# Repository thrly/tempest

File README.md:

# TEMPEST

a 36/38-key split ergonomic keyboard

## Design

- Five columns, three rows, three thumb keys
  - Optional extra key for 36 or 38-key configuration (snap-off pcb)
- Column stagger and splay on the pinky and ring columns
- Powered by nice!nano / pro micro microcontroller
- Optional nice!view display
- Designed for wireless use + battery
- Low profile v1 Choc switches + hotswap sockets
- Reversible PCB
- Uses some components (JST plug, power switch, reset) from the Typeractive Corne design
- Layout designed with [Ergogen](https://ergogen.ceoloide.com/) (see [config.yaml](./ergogen/config.yaml))
- PCB designed with [KiCad](https://www.kicad.org/) (v 9)
- Simple 3D-printable case for both 36 and 38-key layouts

## Firmware

TEMPEST was designed to be used with ZMK. [You can find the ZMK-config repository and a keymap here.](https://github.com/thrly/tempest-zmk)

## Build Guide

[Details on the build and case can be found here.](/build-guide.md)

## Influences

TEMPEST is inspired by and takes influence from:

- [Temper](https://github.com/raeedcho/temper) by raeedcho
- [Bad Temper](https://github.com/essFitt/Bad-Temper/tree/main) by essFitt
- [TOTEM](https://github.com/GEIGEIGEIST/TOTEM) by GEIST
- [FORAGER](https://github.com/carrefinho/forager) by carrefinho
- [Corne](https://github.com/foostan/crkbd) by foostan (and the [Typeractive](https://typeractive.xyz/) version)
- also [Chocofi](https://github.com/pashutk/chocofi), [Sweep](https://github.com/davidphilipbarr/Sweep), and others.

## Thanks

If you build Tempest, I'd _love_ to hear how you get on with it. Please say hello via [thrly.com](https://www.thrly.com) or [instagram](https://www.instagram.com/thrly.xy/).

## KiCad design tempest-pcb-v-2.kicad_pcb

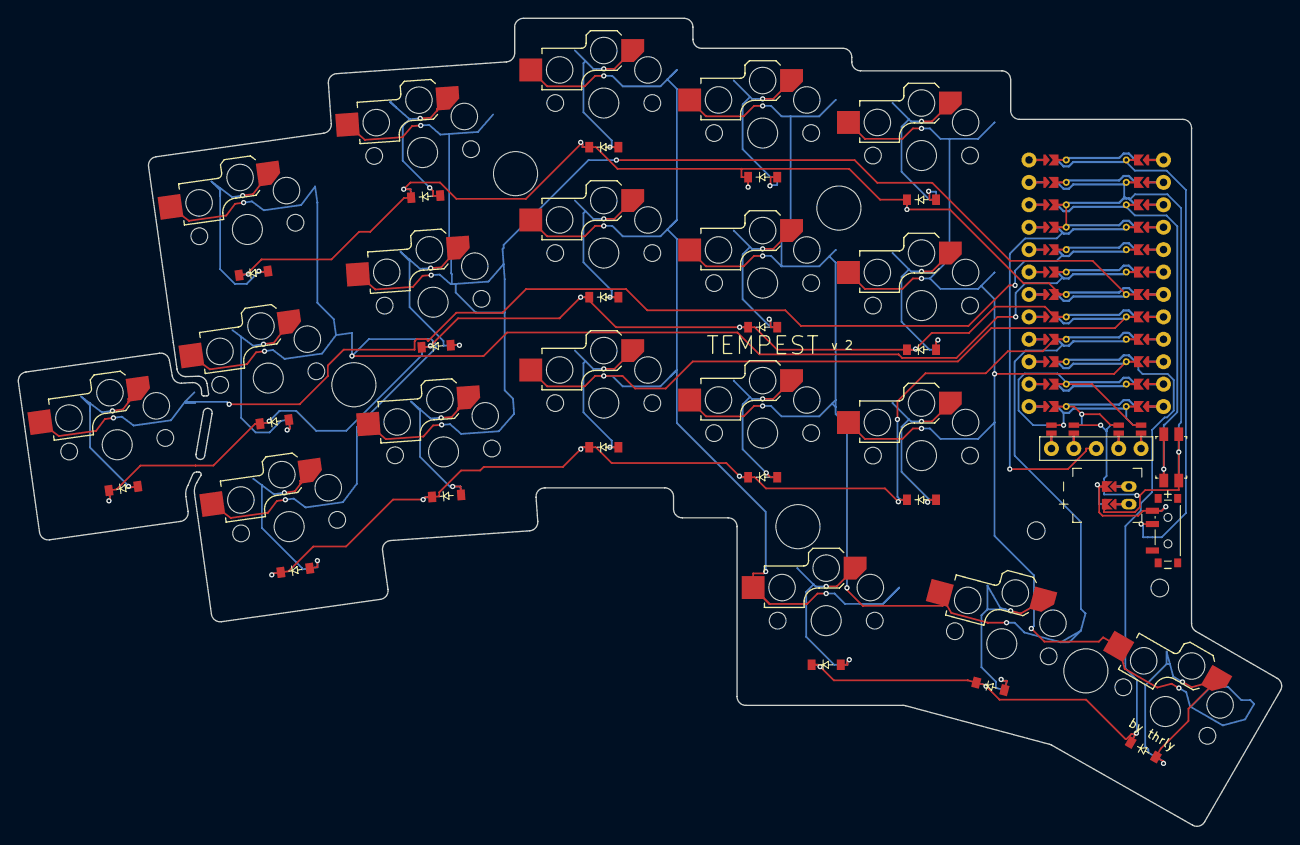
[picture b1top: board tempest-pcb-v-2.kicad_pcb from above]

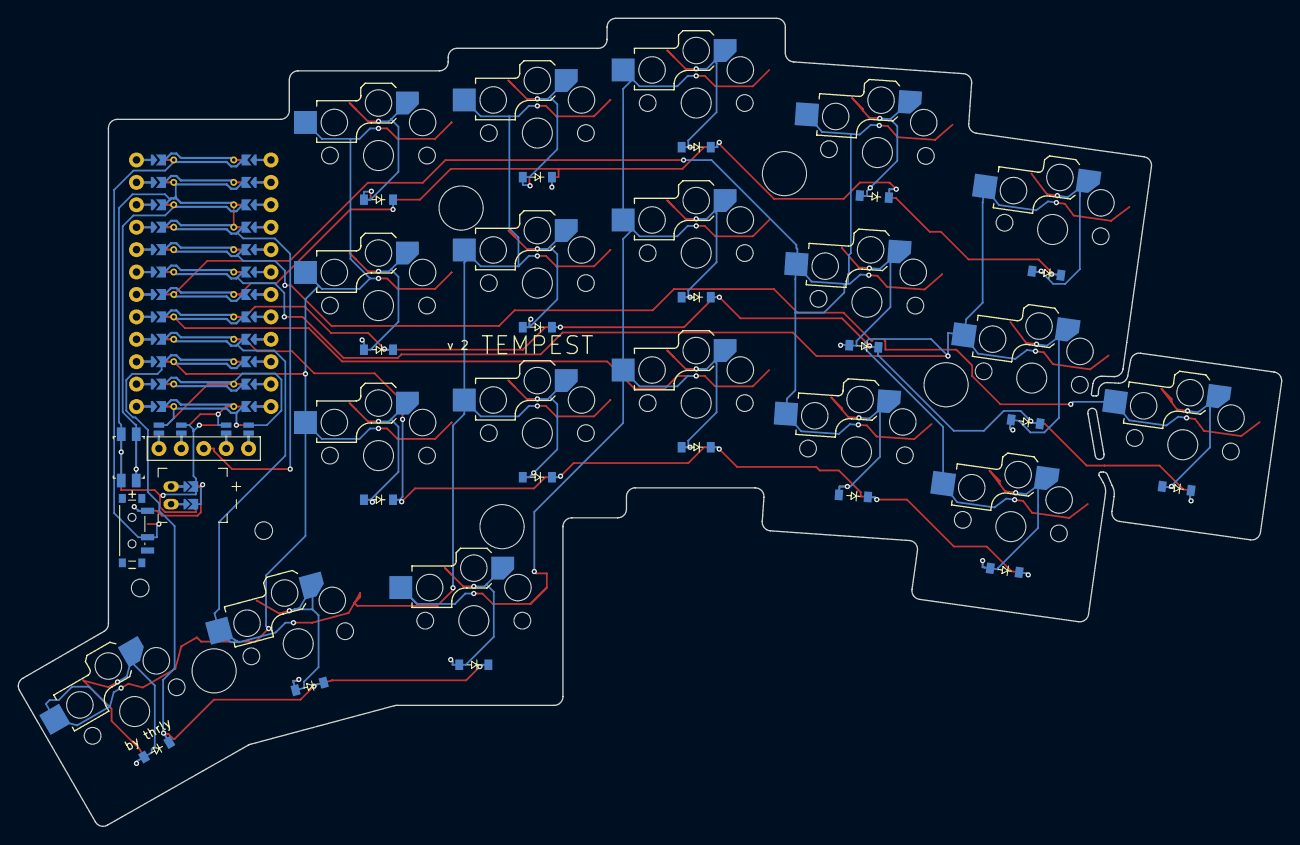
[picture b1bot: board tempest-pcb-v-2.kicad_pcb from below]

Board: 2 copper layers, 143.2 x 91.6 mm, 50 parts (19 on the bottom side), 43 nets.

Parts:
D1, D2, D3, D4, D5, D6, D7, D8, D9, D10, D11, D12, D13, D14, D15, D16, D17, D18, D19: diode_tht_sod123
DISP1: display_nice_view
JST1: battery_connector_jst_ph_2
MCU1: mcu_nice_nano
MH1, MH2, MH3, MH4, MH5, MH6, MH7: mounting_hole_npth
PWR1: power_switch_smd_side
RST1: reset_switch_smd_side
S1, S2, S3, S4, S5, S6, S7, S8, S9, S10, S11, S12, S13, S14, S15, S16, S17, S18, S19: switch_choc_v1_v2

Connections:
BAT_P: JST1.1, PWR1.1, PWR1.3
CS: DISP1.14, DISP1.24, MCU1.112
DISP1_1: DISP1.1, DISP1.10, DISP1.23
DISP1_2: DISP1.2, DISP1.11, DISP1.22
DISP1_4: DISP1.4, DISP1.12, DISP1.21
DISP1_5: DISP1.5, DISP1.13, DISP1.20
GND: DISP1.15, DISP1.25, JST1.2, MCU1.102, MCU1.121, MCU1.122, RST1.1, RST1.3
JST1_1: JST1.11, JST1.21, JST1.31
JST1_2: JST1.12, JST1.22, JST1.32
MOSI: DISP1.17, DISP1.27, MCU1.114
RAW: MCU1.101, PWR1.2
RST: MCU1.103, RST1.2, RST1.4
SCK: DISP1.16, DISP1.26, MCU1.113
VCC: DISP1.3, MCU1.104
col_extra: MCU1.105, S1.2
col_index: MCU1.109, S11.2, S12.2, S13.2, S18.2
col_inner: MCU1.110, S14.2, S15.2, S16.2, S19.2
col_middle: MCU1.108, S8.2, S9.2, S10.2, S17.2
col_pinky: MCU1.106, S2.2, S3.2, S4.2
col_ring: MCU1.107, S5.2, S6.2, S7.2
extra_home: D1.2, S1.1
far_thumb-cluster: D19.2, S19.1
index_bottom: D11.2, S11.1
index_home: D12.2, S12.1
index_top: D13.2, S13.1
inner_bottom: D14.2, S14.1
inner_home: D15.2, S15.1
inner_top: D16.2, S16.1
mid_thumb-cluster: D18.2, S18.1
middle_bottom: D8.2, S8.1
middle_home: D9.2, S9.1
middle_top: D10.2, S10.1
near_thumb-cluster: D17.2, S17.1
pinky_bottom: D2.2, S2.1
pinky_home: D3.2, S3.1
pinky_top: D4.2, S4.1
ring_bottom: D5.2, S5.1
ring_home: D6.2, S6.1
ring_top: D7.2, S7.1
row_bottom: D2.1, D5.1, D8.1, D11.1, D14.1, MCU1.116
row_home: D1.1, D3.1, D6.1, D9.1, D12.1, D15.1, MCU1.117
row_thumb: D17.1, D18.1, D19.1, MCU1.115
row_top: D4.1, D7.1, D10.1, D13.1, D16.1, MCU1.118

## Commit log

2025-03-26 Add ergogen config with keyboard layout and footprints
2025-03-29 Add M2 mounting holes
2025-03-29 update footprint paths to match online ceoloide generator path footprints
2025-03-31 Changed MCU socket sizes to 0.85mm for no-solder headers
2025-03-31 Edit mounting hole placement
2025-04-01 PCB version 0.01
2025-04-03 Add DXF and STL for 1.2mm plates and case test
2025-04-13 Add 0.5mm tolerance fit to plates for better case fit
2025-04-13 Add second case tests, move cases into subfolders
2025-04-30 Change thumb key spacing Update version number to 1.1 gitignore 3D/
2025-04-30 Refine key stagger values (less pronounced) for improved comfort. Narrow spacing on thumb cluster to match other keys.
2025-04-30 Remove future improvements section from README.md
2025-04-30 Fix error on key column nets. Ring, Mid, and Index weren't properly assigned via variable names (they used pin numbers, which didn't work in Kicad!)
2025-04-30 Change MCU plate spacing area to give more room
2025-05-01 Removed outer pcb padding space. Repositioned mcu area lower.
2025-05-01 Add v1.1 pcb and img, removed v0.1
2025-05-02 Tidy folder structure, remove v.0.0 pcb and gerbers. Add gerbers zip.
2025-05-02 Refactor code structure for improved readability and maintainability
2025-05-02 Add wishlist for next version design considerations
2025-05-21 Update README to clarify microcontroller display information
2025-06-03 Added note about spring header hole sizing
2025-06-04 Add photos of Tempest
2025-06-04 Add BOM
2025-06-08 Add Great Wave img
2025-06-08 Add shields
2025-06-12 Update wishlist for next version (v 2) with additional design considerations and improvements
2025-06-12 Add 3D printable case for v 1.1 pcb
2025-06-12 Modify info on YAML
2025-06-12 Add images
2025-06-12 Update README and add build guide.
2025-07-31 v2 ergogen changes
2025-08-01 Clean up config and add change clarification and issue reference #
2025-08-07 added note about fixing mcu pin numbering
2025-08-24 Update pcb, gerbers and README for v2
2025-08-27 Add photos
